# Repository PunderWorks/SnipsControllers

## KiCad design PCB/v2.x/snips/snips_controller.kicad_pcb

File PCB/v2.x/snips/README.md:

# Snips Controller PCB (V2)

A wireless handheld controller for R2-D2 droid operation, designed for use at public events and conventions. Communicates with the droid over Zigbee, in a packetized state-report architecture.

The electrical design is in [Stackup KDL](stackup/board.kdl), using the pinned
Stackup library. The existing [KiCad PCB](snips_controller.kicad_pcb) is linked
through `snips_controller.stackup_sch`; sync it with the Stackup KiCad plugin. Run
`stackup check PCB/v2.x/snips/stackup/board.kdl` from the repository root before syncing.

A STEP model of the assembled board is in [`step/v2.0/snips_controller.step`](step/v2.0/snips_controller.step).

## V2 board

70 x 30 mm, 4 layers: F.Cu signals, In1 solid 3V3, In2 solid GND, B.Cu signals. 1.6 mm thick. Routed, not yet fabricated.

- **Module:** an ESP32-S3-MINI-1U-N8 on the top, between the macro buttons and USB, turned 270 degrees. The 19.2 mm WROOM-1U does not fit the 17.5 mm there. The turn puts the pinless GND edge on the side and the signal pins toward the stick, the OLED and the carrier; pins are assigned by position, as `GPIO_table.md` explains. USB runs about 15 mm as a result, which is well within full-speed limits. Bluetooth and ESP-NOW work with no other radio.
- **XBee:** optional. U_XBEE1 is a row of 12 hand-solder pads on the bottom for a 22 x 17 mm castellated daughter board, which carries the XBee 3 Micro, its decoupling, the RESET pull-up and RC, and the ATTN/BOOTMODE pull-up. The link is UART with flow control, not SPI. RTS and DTR also allow XBee serial firmware recovery through the ESP32. Leave the area inside the pads free of parts; vias there stay tented. See `GPIO_table.md`.
- **Reflow:** the bottom side goes first and the top side last, because Espressif requires a single reflow for the module (datasheet section 12.3). The XBee reflows on its own carrier and never goes upside down, which is what stopped the two modules from sharing this board before.
- **Radio link:** Amidala's droids use XBee Zigbee 3.0, so a Zigbee controller needs the carrier. V2 firmware builds with `pio run -e esp32s3_v2` (upload with `-t upload`). It talks to the XBee over UART in API mode and runs without the carrier.
- **Programming:** USB, through the module's native USB. To force download mode, hold SW_BOOT1 while pressing the power button. RXD0's pull-up holds the latch with no firmware, so a blank board flashes after a 1 s press, with no button held during the upload.
- **No reset button:** the power button turns the board on, and only firmware turns it off. PWR_HOLD is on RXD0, whose pull-up holds the latch through any reset or USB upload, so a blank or hung board stays on until USB and the battery are removed. Keep a watchdog running to recover from a hang. C_LATCH_FB1 gives the latch hysteresis, so that pull-up cannot restart the board at power-off, and R_PWR_EN_PD1 is 22 kΩ so a rising gate cannot couple through it and lift EN.
- **Buttons:** all 13 connect directly to module GPIOs. See `GPIO_table.md`.
- **Power blocks:** the buck, charger and power latch follow V1's relative placement, all on the bottom. Two charger GND vias were moved 0.1-0.75 mm in V1's layout to clear earlier button positions. C_BUCK_IN1 turned 90 degrees with its VSYS pad straight above the VIN pin. BUCK_FB runs around the input cap and hops to F.Cu past the inductor, so both planes shield it; keep it out from under L_BUCK1. The latch is too long to fit whole, so it is split at `PWR_BTN_TRIGGER`: the switch and `PWR_LATCH_G` node sit under the stick, turned 270 degrees, and the inverter sits beside the stick's lower pins. See `diagrams/` for why they are arranged this way.
- **OLED cable:** U_OLED1's opening faces USB, and a Qwiic plug is 7.0 mm wide with its protrusions, so keep top-side parts out of x 0.9-7.9 mm from the mouth at y 52.7 mm down to the MH3 post. Check that a real cable goes in before committing the shell.
- **BOM:** the Value column carries each part's full details, including a capacitor's rated voltage, because fabs read it and the BOM has no voltage column. Keep rail names out of designators: PCBWay queried the V1.2 caps named C_3V3_* as 3.3 V parts, so V2 uses C_MCU_*.
- **Hall sensor:** U_HALL1 is on the bottom at (6.5, 4.75) mm, rotated 180 degrees, forward and left of the stick, 7.8 mm from its nearest pot pin in plan view against about 15.4 mm on V1. A 2 x 2 mm N52 magnet swings up to sit directly under the package centre. Keep at least 1.8 mm from the top of the package to the magnet at full press, or the output clips at the sensor's ±44 mT range. The stick reading against trigger travel still needs a bench test.
- **Mounting:** four Ø2.2 mm unplated holes, MH1-4, at (2.5, 2.6), (27.4, 2.8), (3, 62.5) and (27, 67) from the top-left corner, for M2 self-tapping screws into shell posts. MH3 sits above the power button, which holds the true corner, so a Ø4 post clears `C_DBNC1` by only about 0.15 mm. The carrier has a long shallow chamfer at that corner, which also clears a Ø4 post on the bottom.
- **Battery:** BT1 is a 2-pin JST PH, the common connector on pouch cells this size: pin 1 VBAT, pin 2 GND. R_TS1 ties the charger's TS pin to a fixed 10 kΩ, so there is no pack temperature monitoring. Check the polarity of the cell's lead before plugging it in.
- **USB and status LED:** J_USB1 sits 2 mm right of centre, with its CC resistors and TVS moved with it. D_RGB1 sits between SW_PWR1 and J_USB1, turned 90 degrees.
- **Through-board parts:** the Alps pegs, stick pins, USB stakes and BT1 pins all reach the other side.

## GPIO Assignment

See [`GPIO_table.md`](GPIO_table.md) for every module pin.

## Hardware Overview

| Component | Part | Notes | Layout diagram |
|---|---|---|---|
| MCU and radio | Espressif ESP32-S3-MINI-1U-N8 | Wi-Fi, Bluetooth LE and ESP-NOW, 8 MB flash, 15.4 x 15.4 x 2.4 mm, external antenna | — |
| XBee (optional) | Digi XB3-24Z8UM on a castellated carrier | Zigbee 3.0, +19 dBm, U.FL. Hand-soldered to the underside | — |
| Display | SSD1306 1.3" OLED | 128x64, monochrome, I2C | — |
| Hall trigger | DRV5055A2QDBZR (SOT-23) | Ratiometric linear hall effect, 3.3V. On the bottom of the board under the trigger magnet; senses the field perpendicular to the board. Trigger calibration accepts either magnet polarity | — |
| Thumbstick | GuliKit hall effect module | Native 3.3V, analog X/Y + click | — |
| Macro and boot buttons | Alps SKRPABE010 | 4.2 x 3.2 x 2.5 mm SMD tact switch, 1.57 N, 0.2 mm travel, 100,000 cycles. Footprint checked against the Alps land drawing | — |
| RGB LED | SK6812MINI-HS | Status indicator; specified supply begins at 3.7 V, but board supplies 3.3 V | — |
| Charger | bq25185 | USB/DC input, power path, 4.2V/500mA | [diagram](diagrams/power_charger_layout.md) |
| Buck | TLV62569 | 3.3V output, 2A | [diagram](diagrams/power_buck_layout.md) |
| Battery | Single-cell pouch, 2-pin JST PH | Cell not chosen yet. Set R_ISET1 for it; 604 Ω charges at about 500 mA | — |
| Power switch | AO3401A + AO3400A | Soft latch, hybrid hardware+firmware | [diagram](diagrams/power_control_layout.md) |

## Layout Diagrams

Suggested top-copper floorplans for the three sheets with real layout
stakes — a switching regulator, a linear charger with a thermal pad, and
the soft latch that switches the buck's enable. Each is checked
against the actual component datasheet, not just the schematic. See
[`diagrams/README.md`](diagrams/README.md) for the full list and how the
files are organized.

- [Buck converter](diagrams/power_buck_layout.md) — `/Power_Buck/*` nets in Stackup
- [Charger](diagrams/power_charger_layout.md) — `/Power_Charger/*` nets in Stackup
- [Power latch](diagrams/power_control_layout.md) — `/Power_Control/*` nets in Stackup

## Passives & Support Components

### Decoupling Caps
| Component | Value | Notes |
|---|---|---|
| DRV5055 VCC | 100nF ceramic | |
| GuliKit VCC | 100nF ceramic | |
| SK6812 VCC | 100nF ceramic | Close to supply pin |
| ICM-42670-P | 100nF + 2.2µF on VDD, 10nF on VDDIO | Close to their pins |
| OLED connector | 1µF + 100nF ceramic | |
| bq25185 VIN | 10µF + 100nF ceramic | |
| bq25185 SYS | 10µF + 100nF ceramic | |
| bq25185 BAT | 10µF ceramic | |
| TLV62569 VIN | 10µF ceramic | |
| TLV62569 VOUT | 22µF ceramic | As on V1. TI specifies 10-47 µF |
| ESP32-S3-MINI-1U 3V3 | 10µF + 100nF + 39pF ceramic | As on V1 |
| ESP32-S3-MINI-1U EN | 1µF ceramic | With R_EN_PU1, per Espressif |
| XBee VCC | 10µF + 1µF + 47pF ceramic | On the carrier, per Digi 90001543 p.52 |

### Resistors
| Signal | Value | Notes |
|---|---|---|
| bq25185 STAT1/STAT2 | 10kΩ | Open drain, pulled up to 3V3 |
| bq25185 TS/MR | 10kΩ to GND | Required with no thermistor: floating means no charging |
| I2C SDA/SCL | 4.7kΩ | So the IMU works with no OLED attached |
| Boot button | 10kΩ to 3V3 | R_BOOT_PU1 |
| ESP32 EN | 10kΩ to 3V3 | R_EN_PU1 |
| USB D+/D- | 27Ω series | R_USB_DP1 and R_USB_DM1, as on V1 |
| Trigger output | 1kΩ + 100nF | R_TRIG1 and C_TRIG1, about 1.6 kHz. The DRV5055 must not see a capacitor without a resistor |
| SK6812 DIN | 470Ω | R_RGB1 |

### Buttons
No external parts. Every button wires to GND and a module GPIO, using the internal pull-ups; see [`GPIO_table.md`](GPIO_table.md).

---

## Communication Architecture

The droids use XBee Zigbee 3.0, so the controller joins that network through the XBee on the carrier, over UART in API mode. Each droid has its own coordinator and PAN ID, and all coordinators share one AES key. Without the carrier the ESP32 can use Bluetooth or ESP-NOW.

---

## Bringup Sequence

Recommended bringup order:
1. Current-limited supply on VSYS, with no carrier fitted: press power for 1 s, then check 3V3 and idle current.
2. Flash `pio run -e esp32s3_v2 -t upload` over USB with no button held, with SW_BOOT1 held at power-on if the chip does not enumerate. Never flash the V1 `esp32s3` build. The serial monitor's first line should read `Snips Controller V2, firmware <commit>, reset: <reason>`, and with no carrier, `XBee carrier not found (CTS high)`. Confirm `PWR_HOLD` reads high.
3. Time the shortest press that stays on, at 3.3 V and 4.2 V. The simulation gives under 0.4 s at worst, so a 1 s press is well clear. Run a USB upload with no button held, then type `hang` into the serial monitor: the board should reboot within about 5 s and log `reset: task watchdog`. Power off at least 20 times, on USB and on battery, and scope `PWR_EN` and `PWR_LATCH_G`: the board must stay off every time, since the simulation's margin has not been measured.
4. OLED and ICM-42670-P on I2C.
5. SK6812 RGB LED.
6. Buttons, using the pin table.
7. Charge status on STAT1 and STAT2, and VSYS sense.
8. DRV5055 and thumbstick on the ADC. Sweep the stick and the trigger together to measure how much each moves the other.
9. Solder the carrier on. Check UART traffic, CTS, SLEEP_RQ and ON/SLEEP, then XBee reset, then join a droid's network.

---

## Power Architecture

- Battery → bq25185 (charger and power path, 4.2V, 500mA) → TLV62569 (3.3V buck) → 3V3 for everything, including the carrier.
- Power switch: soft latch (AO3401A PFET + AO3400A NFET) controls the TLV62569 EN pin. USB does not hold it on.
- Boot: press the power button for about a second → latch enables 3V3 → RXD0's pull-up holds the latch through D_OR2 as soon as the chip has power → firmware drives RXD0 high.
- Shutdown: firmware sees a hold on IO21 → graceful shutdown → RXD0 low → the gate decays through R_LATCH_G1 → C_LATCH_FB1 kicks it clear of threshold as PWR_EN falls → power cut after about 0.8-2.6 s, counted from release if the button is still held.
- bq25185 STAT1 and STAT2 go to IO15 and IO14 (open drain, 10kΩ pull-ups to 3V3).
- Battery voltage: VSYS through R_VSYS1/R_VSYS2 to IO10, reading VSYS/3.
- Below about 3.3 V on the battery the buck passes it through, and the DRV5055's minimum is 3.0 V, so the firmware cutoff should sit above that.

## Power Management

Firmware implements tiered power saving:
- **Active**: full brightness OLED, normal polling rate
- **Idle (short timeout)**: OLED dimmed via SSD1306 contrast command
- **Idle (long timeout)**: OLED off
- **Sleep**: MCU sleep, wake on any button press via GPIO interrupt

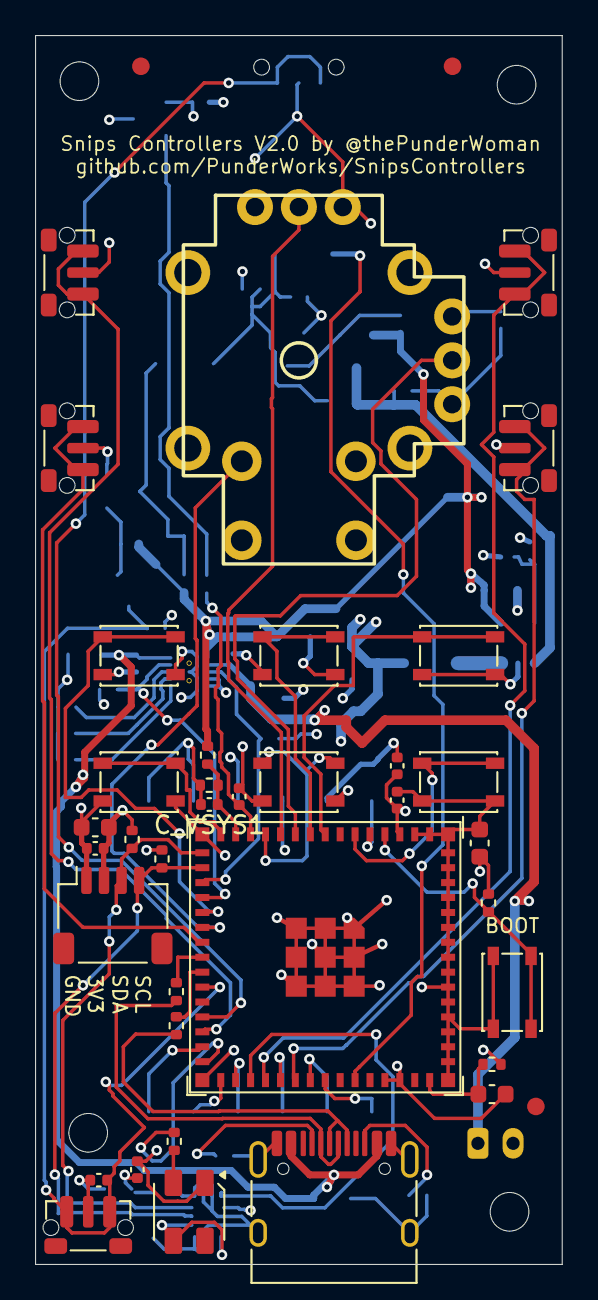
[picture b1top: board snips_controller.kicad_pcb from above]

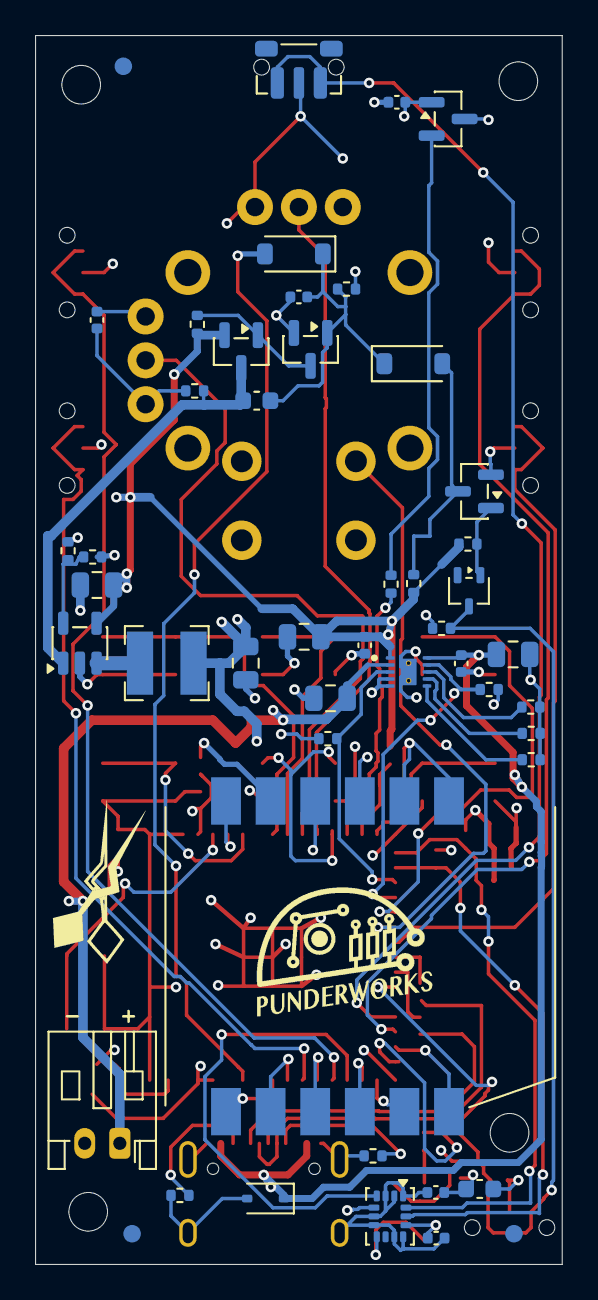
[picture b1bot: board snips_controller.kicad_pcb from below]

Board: 4 copper layers, 30.0 x 70.0 mm, 93 parts (50 on the bottom side), 56 nets.

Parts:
BT1: JST PH 2-pin 2mm | S2B-PH-K(LF)(SN) | JST | Throu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; JST_PH_S2B-PH-K_1x02_P2.00mm_Horizontal
C_BAT1: 10µF 25V X5R ±10% | CL21A106KAYNNNE | Samsung | 0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; C_0805_2012Metric
C_BUCK_IN1: 10µF 25V X5R ±10% | CL21A106KAYNNNE | Samsung | 0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; C_0805_2012Metric
C_BUCK_OUT1: 22µF 25V X5R ±20% | CL21A226MAQNNNE | Samsung | 0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; C_0805_2012Metric
C_DBNC1: 100nF 16V X7R ±10% | CL05B104KO5NNNC | Samsung | 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; C_0402_1005Metric
C_EN1: 1µF 50V X5R ±10% | CL10A105KB8NNNC | Samsung | 06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; C_0603_1608Metric
C_HALL1: 100nF 16V X7R ±10% | CL05B104KO5NNNC | Samsung | 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; C_0402_1005Metric
C_IMU_1: 100nF 16V X7R ±10% | CL05B104KO5NNNC | Samsung | 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; C_0402_1005Metric
C_IMU_2: 2.2µF 10V X7R ±10% | CL10B225KP8NNNC | Samsung | 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; C_0603_1608Metric
C_IMU_3: 10nF 50V X7R ±10% | CL05B103KB5NNNC | Samsung | 0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; C_0402_1005Metric
C_LATCH_FB1: 1µF 50V X5R ±10% | CL10A105KB8NNNC | Samsung | 06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; C_0603_1608Metric
C_LATCH_G1: 1µF 6.3V X5R ±10% | CL05A105KQ5NNNC | Samsung | 0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; C_0402_1005Metric
C_MCU_1: 10µF 10V X5R ±10% | CL10A106KP8NNNC | Samsung | 0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; C_0603_1608Metric
C_MCU_2: 100nF 16V X7R ±10% | CL05B104KO5NNNC | Samsung | 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; C_0402_1005Metric
C_MCU_3: 39pF 50V NP0 ±5% | CC0402JRNPO9BN390 | Yageo | 04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; C_0402_1005Metric
C_OLED_1: 1µF 50V X5R ±10% | CL10A105KB8NNNC | Samsung | 06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; C_0603_1608Metric
C_OLED_2: 100nF 16V X7R ±10% | CL05B104KO5NNNC | Samsung | 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; C_0402_1005Metric
C_RGB1: 100nF 16V X7R ±10% | CL05B104KO5NNNC | Samsung | 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; C_0402_1005Metric
C_STICK1: 100nF 16V X7R ±10% | CL05B104KO5NNNC | Samsung | 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; C_0402_1005Metric
C_SYS_1: 10µF 25V X5R ±10% | CL21A106KAYNNNE | Samsung | 0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; C_0805_2012Metric
C_SYS_2: 100nF 16V X7R ±10% | CL05B104KO5NNNC | Samsung | 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; C_0402_1005Metric
C_TRIG1: 100nF 16V X7R ±10% | CL05B104KO5NNNC | Samsung | 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; C_0402_1005Metric
C_VIN_1: 10µF 25V X5R ±10% | CL21A106KAYNNNE | Samsung | 0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; C_0805_2012Metric
C_VIN_2: 100nF 16V X7R ±10% | CL05B104KO5NNNC | Samsung | 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; C_0402_1005Metric
C_VSYS1: 100nF 16V X7R ±10% | CL05B104KO5NNNC | Samsung | 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; C_0402_1005Metric
D_INV_ISO1: Schottky diode 30V 200mA | BAT54W-7-F | Diodes In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; SOT-323_SC-70
D_OR1, D_OR2: 1N4148W switching diode 75V 150mA | 1N4148W | ST 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; D_SOD-123
D_RGB1: Addressable RGB LED | SK6812MINI-HS | OPSCO | 3.5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; SK6812MINI-HS-012
D_VBUS_TVS1: TVS diode 5V bidirectional | TPPESD5V0S1BA | TECH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; D_SOD-323
FID1, FID2, FID3, FID4, FID5, FID6: Fiducial_1mm_Mask2mm
J_STICK1: Hall thumbstick | GuliKit_Thumbstick | GuliKit | 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; GuliKit_HallStick
J_USB1: USB-C receptacle 16-pin | TYPE-C-31-M-12 | Hropar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; USB_C_Receptacle_HRO_TYPE-C-31-M-12
LOGO2: LOGO
LOGO4: PunderWorks_Logo_10mm
L_BUCK1: 2.2µH ±20% 2.9A 44mΩ power inductor | SRN4018-2R2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; L_Bourns-SRN4018
MH1, MH2, MH3, MH4: MountingHole_2.2mm_M2_ISO14580
Q_INV1: NPN transistor 40V 200mA hFE 100-300 | MMBT3904(R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; SOT-23
Q_LATCH1: N-channel MOSFET 30V 5.7A | AO3400A | AOS | SOT-23; SOT-23
Q_PWR1: P-channel MOSFET 30V 4A | AO3401A | AOS | SOT-23; SOT-23
R_BOOT_PU1: 10kΩ ±1% 62.5mW | 0402WGF1002TCE | UNI-ROYAL | 04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; R_0402_1005Metric
R_BTN_PU1: 100kΩ ±1% 62.5mW | 0402WGF1003TCE | UNI-ROYAL | 0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; R_0402_1005Metric
R_CC1, R_CC2: 5.1kΩ ±1% 62.5mW | 0402WGF5101TCE | UNI-ROYAL | 0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; R_0402_1005Metric
R_EN_PU1: 10kΩ ±1% 62.5mW | 0402WGF1002TCE | UNI-ROYAL | 04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; R_0402_1005Metric
R_FB1: 255kΩ ±1% 62.5mW | RC0402FR-07255KL | Yageo | 0402; R_0402_1005Metric
R_FB2: 56.2kΩ ±1% 62.5mW | RC0402FR-0756K2L | Yageo | 04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; R_0402_1005Metric
R_GATE1: 100kΩ ±1% 62.5mW | 0402WGF1003TCE | UNI-ROYAL | 0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; R_0402_1005Metric
R_I2C_SCL1, R_I2C_SDA1: 4.7kΩ ±1% 62.5mW | 0402WGF4701TCE | UNI-ROYAL | 0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; R_0402_1005Metric
R_INV_BASE1: 220kΩ ±1% 62.5mW | 0402WGF2203TCE | UNI-ROYAL | 0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; R_0402_1005Metric
R_INV_PU1: 220kΩ ±1% 62.5mW | 0402WGF2203TCE | UNI-ROYAL | 0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; R_0402_1005Metric
R_ISET1: 604Ω ±1% 62.5mW | AC0402FR-07604RL | Yageo | 0402; R_0402_1005Metric
R_LATCH_G1: 1MΩ ±1% 62.5mW | 0402WGF1004TCE | UNI-ROYAL | 0402; R_0402_1005Metric
R_PWR_EN_PD1: 22kΩ ±1% 62.5mW | 0402WGF2202TCE | UNI-ROYAL | 04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; R_0402_1005Metric
R_RGB1: 470Ω ±1% 62.5mW | 0402WGF4700TCE | UNI-ROYAL | 04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; R_0402_1005Metric
R_STAT1, R_STAT2: 10kΩ ±1% 62.5mW | 0402WGF1002TCE | UNI-ROYAL | 04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; R_0402_1005Metric
R_TRIG1: 1kΩ ±1% 62.5mW | 0402WGF1001TCE | UNI-ROYAL | 0402; R_0402_1005Metric
R_TS1: 10kΩ ±1% 62.5mW | 0402WGF1002TCE | UNI-ROYAL | 04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; R_0402_1005Metric
R_USB_DM1: 27Ω ±1% 62.5mW | RC0402FR-0727RL | Yageo | 0402; R_0402_1005Metric
R_USB_DP1: 27Ω ±1% 62.5mW | RC0402FR-0727RL | Yageo | 0402; R_0402_1005Metric
R_VSET1: 18kΩ ±1% 62.5mW | RC0402FR-0718KL | Yageo | 0402; R_0402_1005Metric
R_VSYS1: 200kΩ ±1% 62.5mW | 0402WGF2003TCE | UNI-ROYAL | 0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; R_0402_1005Metric
R_VSYS2: 100kΩ ±1% 62.5mW | 0402WGF1003TCE | UNI-ROYAL | 0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; R_0402_1005Metric
SW_BOOT1: Tact switch 1.6N 100k cycles | SKRPABE010 | Alps 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; SW_Alps_SKRP
SW_MACRO1, SW_MACRO2, SW_MACRO3, SW_MACRO4, SW_MACRO5, SW_MACRO6: Tact switch 1.6N 100k cycles | SKRPABE010 | Alps 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; SW_Alps_SKRP
SW_PWR1: Side-push tact switch 1.6N 100k cycles | SKRTLAE0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; SW_Push_1P1T-MP_NO_Horizontal_Alps_SKRTLAE010
SW_THR_DN1: Side-push tact switch 1.6N 100k cycles | SKRTLAE0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; SW_Push_1P1T-MP_NO_Horizontal_Alps_SKRTLAE010
SW_THR_UP1: Side-push tact switch 1.6N 100k cycles | SKRTLAE0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; SW_Push_1P1T-MP_NO_Horizontal_Alps_SKRTLAE010
SW_TRIG_DIG1: Side-push tact switch 1.6N 100k cycles | SKRTLAE0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; SW_Push_1P1T-MP_NO_Horizontal_Alps_SKRTLAE010
SW_VOL_DN1: Side-push tact switch 1.6N 100k cycles | SKRTLAE0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; SW_Push_1P1T-MP_NO_Horizontal_Alps_SKRTLAE010
SW_VOL_UP1: Side-push tact switch 1.6N 100k cycles | SKRTLAE0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; SW_Push_1P1T-MP_NO_Horizontal_Alps_SKRTLAE010
U_BUCK1: Adjustable buck converter 2A | TLV62569DBVR | TI 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; SOT-23-5
U_CHG1: 1-cell Li-ion charger 1A | BQ25185DLHR | TI | WSO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; IC_BQ25185DLHR
U_HALL1: Linear hall sensor A2 ±42mT | DRV5055A2QDBZR | TI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; SOT-23
U_IMU1: 6-axis IMU | ICM-42670-P | TDK InvenSense | LGA-1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; LGA-14_3x2.5mm_P0.5mm_LayoutBorder3x4y
U_MCU1: Wi-Fi BLE module 8MB flash no PSRAM | ESP32-S3-MI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; ESP32-S3-MINI-1U
U_OLED1: JST SH 4-pin 1mm Qwiic | SM04B-SRSS-TB(LF)(SN) | 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; JST_SH_SM04B-SRSS-TB_1x04-1MP_P1.00mm_Horizontal
U_XBEE1: XBee carrier pads no part | Snips XBee carrier | 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; XBee_Carrier_Castellated

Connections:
3V3: C_BUCK_OUT1.1, C_HALL1.1, C_IMU_1.1, C_IMU_2.1, C_IMU_3.1, C_MCU_1.1, C_MCU_2.1, C_MCU_3.1, C_OLED_1.1, C_OLED_2.1, C_RGB1.1, C_STICK1.1, D_RGB1.3, J_STICK1.3 (X_HI), J_STICK1.3' (Y_HI), L_BUCK1.2, R_BOOT_PU1.2, R_BTN_PU1.1, R_EN_PU1.2, R_FB1.2, R_I2C_SCL1.1, R_I2C_SDA1.1, R_STAT1.2, R_STAT2.2, U_HALL1.1, U_IMU1.5, U_IMU1.8, U_IMU1.12, U_MCU1.3, U_OLED1.2 (VCC), U_XBEE1.9, U_XBEE1.10
/Accelerometer/I2C_SCL: R_I2C_SCL1.2, U_IMU1.13, U_MCU1.17, U_OLED1.4 (SCL)
/Accelerometer/I2C_SDA: R_I2C_SDA1.2, U_IMU1.14, U_MCU1.16, U_OLED1.3 (SDA)
/Buttons_Direct/BTN_MACRO1: SW_MACRO1.1, U_MCU1.20
/Buttons_Direct/BTN_MACRO2: SW_MACRO2.1, U_MCU1.9
/Buttons_Direct/BTN_MACRO3: SW_MACRO3.1, U_MCU1.8
/Buttons_Direct/BTN_MACRO4: SW_MACRO4.1, U_MCU1.15
/Buttons_Direct/BTN_MACRO5: SW_MACRO5.1, U_MCU1.12
/Buttons_Direct/BTN_MACRO6: SW_MACRO6.1, U_MCU1.6
/Buttons_Direct/BTN_THR_DN: SW_THR_DN1.1, U_MCU1.22
/Buttons_Direct/BTN_THR_UP: SW_THR_UP1.1, U_MCU1.28
/Buttons_Direct/BTN_TRIG_DIG: SW_TRIG_DIG1.1, U_MCU1.27
/Buttons_Direct/BTN_VOL_DN: SW_VOL_DN1.1, U_MCU1.36
/Buttons_Direct/BTN_VOL_UP: SW_VOL_UP1.1, U_MCU1.34
/Hall_Trigger/TRIG_ADC: C_TRIG1.1, R_TRIG1.2, U_MCU1.13
/Hall_Trigger/TRIG_ANALOG: R_TRIG1.1, U_HALL1.2
/MCU_Core/BTN_STICK: J_STICK1.a (SW_A), U_MCU1.21
/MCU_Core/MCU_BOOT: R_BOOT_PU1.1, SW_BOOT1.2, U_MCU1.4
/MCU_Core/MCU_EN: C_EN1.1, R_EN_PU1.1, U_MCU1.45
/MCU_Core/PWR_BTN_SENSE: C_DBNC1.1, D_INV_ISO1.3 (K), R_BTN_PU1.2, SW_PWR1.1, U_MCU1.25
/MCU_Core/PWR_HOLD: D_OR2.2 (A), U_MCU1.40
/MCU_Core/RGB_DIN: R_RGB1.2, U_MCU1.30
/MCU_Core/STAT1: R_STAT1.1, U_CHG1.9 (STAT1), U_MCU1.19
/MCU_Core/STAT2: R_STAT2.1, U_CHG1.3 (STAT2), U_MCU1.18
/MCU_Core/STICK_X: J_STICK1.2 (X_OUT), U_MCU1.11
/MCU_Core/STICK_Y: J_STICK1.2' (Y_OUT), U_MCU1.10
/MCU_Core/USB_DM: J_USB1.A7 (D-), J_USB1.B7 (D-), R_USB_DM1.1
/MCU_Core/USB_DM_MCU: R_USB_DM1.2, U_MCU1.23
/MCU_Core/USB_DP: J_USB1.A6 (D+), J_USB1.B6 (D+), R_USB_DP1.1
/MCU_Core/USB_DP_MCU: R_USB_DP1.2, U_MCU1.24
/MCU_Core/VSYS_SENSE: C_VSYS1.1, R_VSYS1.2, R_VSYS2.1, U_MCU1.14
/Power_Buck/BUCK_FB: R_FB1.1, R_FB2.1, U_BUCK1.5 (FB)
/Power_Buck/BUCK_SW: L_BUCK1.1, U_BUCK1.3 (SW)
/Power_Buck/PWR_EN: C_LATCH_FB1.1, Q_PWR1.3 (D), R_PWR_EN_PD1.1, U_BUCK1.1 (EN)
/Power_Charger/CHG_ISET: R_ISET1.1, U_CHG1.8 (ISET)
/Power_Charger/CHG_TS: R_TS1.1, U_CHG1.6 (TS/MR)
/Power_Charger/CHG_VSET: R_VSET1.1, U_CHG1.7 (ILIM/VSET)
/Power_Control/PWR_BTN_INV_BASE: D_INV_ISO1.1 (A), Q_INV1.1 (B), R_INV_BASE1.2
/Power_Control/PWR_BTN_TRIGGER: D_OR1.2 (A), Q_INV1.3 (C), R_INV_PU1.2
/Power_Control/PWR_GATE: Q_LATCH1.3 (D), Q_PWR1.1 (G), R_GATE1.2
/Power_Control/PWR_LATCH_G: C_LATCH_FB1.2, C_LATCH_G1.2, D_OR1.1 (K), D_OR2.1 (K), Q_LATCH1.1 (G), R_LATCH_G1.2
/RGB_LED/RGB_DIN_R: D_RGB1.2, R_RGB1.1
/USB_C/USB_CC1: J_USB1.A5 (CC1), R_CC1.1
/USB_C/USB_CC2: J_USB1.B5 (CC2), R_CC2.1
/XBee/XBEE_CTS: U_MCU1.29, U_XBEE1.1
/XBee/XBEE_DIN: U_MCU1.31, U_XBEE1.2
/XBee/XBEE_DOUT: U_MCU1.32, U_XBEE1.3
/XBee/XBEE_ON_SLEEP: U_MCU1.37, U_XBEE1.5
/XBee/XBEE_RESET: U_MCU1.38, U_XBEE1.6
/XBee/XBEE_RTS: U_MCU1.35, U_XBEE1.4
/XBee/XBEE_SLEEP_RQ: U_MCU1.5, U_XBEE1.7
ACCEL_INT1: U_IMU1.4, U_MCU1.33
GND: BT1.2, C_BAT1.2, C_BUCK_IN1.2, C_BUCK_OUT1.2, C_DBNC1.2, C_EN1.2, C_HALL1.2, C_IMU_1.2, C_IMU_2.2, C_IMU_3.2, C_LATCH_G1.1, C_MCU_1.2, C_MCU_2.2, C_MCU_3.2, C_OLED_1.2, C_OLED_2.2, C_RGB1.2, C_STICK1.2, C_SYS_1.2, C_SYS_2.2, C_TRIG1.2, C_VIN_1.2, C_VIN_2.2, C_VSYS1.2, D_RGB1.1, D_VBUS_TVS1.2 (A2), J_STICK1.1 (X_LO), J_STICK1.1' (Y_LO), J_STICK1.c (SW_C), J_USB1.A1 (GND), J_USB1.A12 (GND), J_USB1.B1 (GND), J_USB1.B12 (GND), J_USB1.SH (SHIELD), Q_INV1.2 (E), Q_LATCH1.2 (S), R_CC1.2, R_CC2.2, R_FB2.2, R_ISET1.2, R_LATCH_G1.1, R_PWR_EN_PD1.2, R_TS1.2, R_VSET1.2, R_VSYS2.2, SW_BOOT1.1, SW_MACRO1.2, SW_MACRO2.2, SW_MACRO3.2, SW_MACRO4.2, SW_MACRO5.2, SW_MACRO6.2, SW_PWR1.2, SW_THR_DN1.2, SW_THR_UP1.2, SW_TRIG_DIG1.2, SW_VOL_DN1.2, SW_VOL_UP1.2, U_BUCK1.2 (GND), U_CHG1.4 (~CE), U_CHG1.5 (GND), U_CHG1.11 (THERMAL_PAD), U_CHG1.12, U_CHG1.13, U_HALL1.3, U_IMU1.1, U_IMU1.2, U_IMU1.3, U_IMU1.6, U_IMU1.7, U_IMU1.10, U_IMU1.11, U_MCU1.1, U_MCU1.2, U_MCU1.42, U_MCU1.43, U_MCU1.46, U_MCU1.47, U_MCU1.48, U_MCU1.49, U_MCU1.50, U_MCU1.51, U_MCU1.52, U_MCU1.53, U_MCU1.54, U_MCU1.55, U_MCU1.56, U_MCU1.57, U_MCU1.58, U_MCU1.59, U_MCU1.60, U_MCU1.61, U_MCU1.62, U_MCU1.63, U_MCU1.64, U_MCU1.65, U_OLED1.1 (GND), U_XBEE1.8, U_XBEE1.11, U_XBEE1.12
VBAT: BT1.1, C_BAT1.1, U_CHG1.2 (BAT)
VBUS: C_VIN_1.1, C_VIN_2.1, D_VBUS_TVS1.1 (A1), J_USB1.A4 (VBUS), J_USB1.A9 (VBUS), J_USB1.B4 (VBUS), J_USB1.B9 (VBUS), U_CHG1.10 (IN)
VSYS: C_BUCK_IN1.1, C_SYS_1.1, C_SYS_2.1, Q_PWR1.2 (S), R_GATE1.1, R_INV_BASE1.1, R_INV_PU1.1, R_VSYS1.1, U_BUCK1.4 (VIN), U_CHG1.1 (SYS)

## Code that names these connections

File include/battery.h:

#pragma once

// Pure logic for battery percentage and bq25185 charge-status decoding.
// Knows nothing about real ADC/GPIO reads — SnipsController.ino does the
// actual analogRead()/digitalRead() and passes raw values in.
enum class ChargeState {
  kDone,               // charge complete, sleep mode, or charging disabled
  kCharging,           // normal charging in progress (incl. auto-recharge)
  kRecoverableFault,   // VIN_OVP, TS hot/cold, or system short
  kLatchedFault,       // ILIM/ISET short, BATOCP, or safety timer expired
};

// Whether the controller is on USB, as far as the board can tell. VBUS
// reaches only the charger's IN pin (no GPIO senses it), so USB shows up
// only indirectly: a computer's USB host is seen by the ESP32-S3's
// native USB, and the charger reporting kCharging means VBUS is present.
// A power-only supply (wall charger, power bank) with the charger
// reporting done is indistinguishable from running on battery: STAT
// reads the same for "charge complete" and "no input power".
enum class UsbPower {
  kNotDetected,  // On battery, or USB power the board can't see.
  kPowerOnly,    // Charging, so VBUS is present, but no USB host.
  kHost,         // A USB host (computer) is connected.
};

UsbPower usbPowerFor(bool usbHostConnected, ChargeState chargeState);

// Short lowercase description for Serial logging, e.g. "host connected".
const char *usbPowerName(UsbPower usbPower);

class BatteryMonitor {
 public:
  // Truth table is bq25185 datasheet (SLUSF65A) Table 7-2 "Status Pins
  // State Table" — stat1High/stat2High are the STAT1/STAT2 pin states as
  // read directly (both are open-drain with an external pull-up to 3V3,
  // so HIGH/LOW here is the real electrical state, no polarity inversion).
  ChargeState chargeStateFor(bool stat1High, bool stat2High) const;

  // Raw ADC (0-4095, ESP32 12-bit) -> battery percentage (0-100), via the
  // VSYS divide-by-3 network (R_VSYS1/R_VSYS2, see PCB/v1.x/GPIO_table.md) and a
  // linear approximation between empty/full cell voltage. Assumes the ADC
  // is configured for its default ~3.3V full-scale range — confirm against
  // real hardware, and note a linear curve is a simplification of a real
  // Li-ion discharge curve, good enough for a v1 estimate.
  int percentFor(int rawAdc) const;

  // Same mapping as percentFor(), but unrounded (0.0-100.0) and taking a
  // fractional raw reading, so an averaged ADC value keeps its precision.
  float percentExactFor(float rawAdc) const;

 private:
  static constexpr int kAdcMaxCounts = 4095;
  static constexpr float kAdcFullScaleVolts = 3.3f;
  static constexpr float kVsysDividerRatio = 3.0f;
  static constexpr float kEmptyVoltage = 3.0f;
  static constexpr float kFullVoltage = 4.2f;
};

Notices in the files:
parts and their libraries:
Adapted from dbenoy/thumbstick-breakout (CC-BY-SA 4.0, Copyright (c) Daniel Benoy), which itself used the C&K THB001P datasheet for dimensions.
Adapted from dbenoy/thumbstick-breakout (CC-BY-SA 4.0, Copyright (c) Daniel Benoy).
